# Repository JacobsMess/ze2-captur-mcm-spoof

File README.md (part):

# ZE2 Captur MCM spoof board

> **Current version: v0.11, the head of `main`.** Everything in this
> repository (board, fab files in `hw/out/jlc/`, firmware, images, docs) describes v0.11. Earlier versions are kept
> only in the git history and are **superseded: do not order from them**. See [Versions](#versions).

A man-in-the-middle board that lets a stock Honda Insight ZE2 run on a Renault Captur E-Tech
lithium pack. The stock MCM stays in charge; the board only changes what it measures: cell taps,
pack temperatures and the current-sensor signal. It also sits on the car's CAN buses. Later,
with the MCM removed, the same board becomes the CAN gateway for a ZombieVerter and a Toyota
inverter.

> **Status: untested design, v0.11.** No boards have been made. v0.6, v0.7 and v0.10 fold in three design reviews;
> v0.8 lets the board measure or cope with the remaining unknowns itself; v0.9 moved the routing to
> [KiCadRoutingTools](https://github.com/drandyhaas/KiCadRoutingTools); v0.11 applies the VND7050AJ, Littelfuse 242,
> TPS3431 and ESP32-S3 datasheets (precharge-coil current sense, 100 ohm tap-ladder ends, fuse land pattern). Bring-up and vehicle checks are in
> [docs/BRINGUP.md](docs/BRINGUP.md). Several parts are placeholders (listed
> [below](#before-ordering)). The BOM carries LCSC numbers, Basic or Preferred wherever JLC has one. The design was
> produced with an AI assistant from my brief and is up for review ([feedback](#feedback) welcome).
> Don't connect it to a pack on the strength of this README.

| | |
|---|---|
| Car | Honda Insight ZE2 (JDM), stock IMA: MCM, MPI, DC-DC, junction board |
| Pack | Renault Captur E-Tech 1.2 kWh, 68S (2 x 34S), own master/satellite BMS and contactors |
| Stage 1 | modules in parallel, 34S2P, about 130 V; stock MCM fed spoofed signals |
| Stage 2 | 68S, about 260 V, MCM removed, ZombieVerter V1 + Toyota inverter (OpenInverter logic board) |
| MCU | ESP32-S3-WROOM-1-N8R2 (8 MB flash, Wi-Fi: SavvyCAN streaming over GVRET, OTA updates) |
| CAN | 4 buses: CAN1 EV (TWAI), CAN2/CAN3 the MCM and PCM halves of the IMA bus, CAN4 dash tap (MCP2518FD each, 32-frame receive FIFO) |
| Spoofing | 9 cell taps (resistor divider off the real pack bus), 3 NTC lines (DAC + op-amps), Hall current offset (+/-125 mV) |
| Contactors | Captur contactors and precharge driven by the board: high-side drivers + low-side master FET behind a watchdog-cleared enable latch |
| HV side | stage 1 only, rated 150 V, 5.6 mm copper-free band, short slots under the three isolation parts |
| Board | 120 x 98 mm, 4 layers, 1.6 mm, parts on top |

## How it works

- **Cell taps:** a resistor divider fed from the real pack bus (through a 250 V DC fuse and 100 ohm at
  each end, switched by two optoMOS) gives the MCM nine balanced taps. The taps are switched on only once
  the contactors are verified closed and the analog island is answering. If the board loses power the
  optoMOS open, the taps float and the MCM sets the IMA light and stops using the pack.
- **Temperatures:** a DAC and op-amp buffers drive the three NTC lines, mapping the Captur
  temperatures onto the Honda curve.
- **SOC:** a small DAC offset added to the Hall sensor signal nudges the MCM's own coulomb count to
  track the real pack, so it stops regen near full and assist near empty by itself.
- **Analog island:** the DAC, op-amps and readback ADCs run from the MCM's 5 V sensor supply,
  isolated from the rest by an I2C isolator, so everything is ratiometric to the MCM.
- **Captur contactors:** closed by the board at key-on, before the MCM looks at the pack. An
  AMC3311 isolated amplifier (with its own isolated supply) on the bus checks precharge and
  contactor welding.
- **CAN:** CAN2 and CAN3 split the IMA bus. A DPDT relay (K4) joins the halves whenever the board is
  unpowered. Each split half can be terminated at the board end by a 120 ohm resistor, connected
  only while K4 is energised: the PCM side through K4's spare normally-open contacts, the MCM side
  through a photoMOS driven alongside the coil. Each has a solder jumper, open by default; measure
  CANH-CANL on each half with the bus split (about 120 ohm: close it; about 60 ohm: leave it).
  CAN4 is a plain tap on the dash bus. CAN2-4 transceivers stay in hardware silent mode until a
  solder jumper is closed. Bypass is the factory setting (`mitm` off in NVS); when splitting is enabled,
  K4 is energised only after both CAN controllers confirm normal mode, and a hung control loop is reset by
  the task watchdog, which releases K4.
- **Protection:** steer SOC first; then float the tap divider so the MCM faults; last, open the
  Captur contactors. The master enable is a flip-flop that the firmware's watchdog kicks clock
  in; if the firmware hangs the watchdog clears it. A stall is a latched fault: nothing closes again
  until a key-off, which the ADC reads with hysteresis and a 2 s dwell so a crank dip doesn't count.
  Contactor, sensing and weld faults all end the same way, as does losing the ignition reading for
  0.5 s. A reset while running (brownout, watchdog, panic) starts tripped and stays so until the next
  power cycle. No regen below about 5 C.
- **Closing the contactors:** the Captur has two, main+ and precharge; pack negative is hard-wired. With
  both coils off the link (watched by the AMC3311) must be dead, which rules out a weld. Then precharge,
  then main+ with precharge still held until it has picked up, then precharge off for 300 ms: the link
  must hold at the pack voltage. A charged link reads ~100 % with main+ open too, so the check is that it
  doesn't decay (calibrated on the bench, [BRINGUP](docs/BRINGUP.md)). The precharge driver's current sense
  must show coil current while precharging and none once closed. The close aborts, latched, on a
  precharge deadline, a link reading above the pack, or a soft trip before it finishes. A soft trip keeps a
  closed pack closed but never starts a close.
- **Captur BMS:** kept awake by the 0x0F5 frame every 20 ms (counter + CRC-8) and read with UDS (29-bit,
  read-only) for the extreme cells, the cell sum, temperatures and SOC, as decoded on the bench. The
  precharge target is the cell sum scaled to the series string (half of it in 34S2P), and the sum must
  agree with 68 x the extreme cells.
- **If the board dies:** the IMA bus rejoins and the dash is unaffected, but the pack drops out on
  purpose. The car runs engine-only with the IMA light, and the 12 V battery isn't charged (the
  DC-DC runs off the pack).

## Schematic

Block-level sheets with the key part values, drawn by [`docs/schematic.py`](docs/schematic.py).
The netlist itself is [`hw/parts.json`](hw/parts.json), written by
[`hw/build_board.py`](hw/build_board.py).

<details>
<summary><b>The five sheets</b></summary>

</details>

## Circuit board

The HV strip is on the right. Only three parts cross the gap to it, and each is an isolation part:
the two AQV214EH optoMOS (K2, K3) and the AMC3311 (U12). There is a
1.2 mm slot under each of those, where dirt or flux trapped under the body could bridge pads. At
150 V or less the 5.6 mm band gives enough creepage without a slot elsewhere. The pack terminal
J3 overhangs the top edge with its wire entry facing out, and the USB-C face sits about 0.85 mm past the bottom edge.

## Before ordering

- Pinouts to check against datasheets: VND7050AJ (custom PowerSSO-16 footprint in `hw/lib`),
  TPS3431, SN74LVC1G74 and SN74LVC1G17 (watchdog latch), SN74LV1T34 (5 V gate buffers), AMC3311, AQY212GS,
  H24VNT2B, and the SMMS0630 inductor on the SRP7028A land pattern.
- Land patterns drawn from datasheet dimensions (`hw/lib/ze2.pretty`): the AQV214EHA (Panasonic's 1.5 x 1.9 mm
  lands on 8.3 mm rows) and the Littelfuse 242 fuse (end-cap lands sized from the 3.0 x 8.4 mm body: check
  against Littelfuse's drawing).
- The Captur coils are measured: main 22.8 ohm (0.535 A at 12 V, pulls in at 5.5 V), precharge about
  56 ohm (0.2 A, 6.8 V), so the coil path carries under 0.8 A. Pump: any 12 V pump under about 3 A
  (see [Pump](#pump)); nothing to measure before ordering.
- Wire the pack as below (the coils have no internal diode, so driving them from the high side with the
  common pin 7 on the return is fine).
- K4: beep-test a G6K-2F-Y before fitting. Pins 3/6 must be the commons (IMA side), 2/7 the
  normally-closed contacts (MCM side).
- AMC3311 stock at JLC is low: check before ordering, or fit by hand.
- Check rotations in JLC's placement preview, especially U8/U9 (custom footprint).
- Conformal-coat the HV strip. Every HV-class net (bus, ladder, taps, sense chain) keeps 0.7 mm from the
  bus-negative side by a DRC rule (`hw/ze2-mcm-spoof.kicad_dru`); IPC-2221 B2 asks 0.6 mm uncoated at 101-150 V.
  Creepage across the assembled parts, the harness and the enclosure still needs checking on the built unit.
- J5 (USB-C): KiCad's footprint puts the peg holes 0.19 mm from pads A/B. Common on JLC boards, but check
  their NPTH-to-copper rule when ordering.
- Check the Captur BMS protects both parallel strings in 34S2P.
- Nothing on the car or the pack needs measuring before ordering. What used to be on this list is now
  handled by the board itself:
  - NTC pull-ups: measured by the board at each start-up and trimmed by readback (only the Honda sensor's
    curve is assumed; check it against the MCM's reported battery temperature in the first log).
  - Tap input impedance: the tap ladder is 10k (0.13 W), so even a 1 Mohm MCM input shifts a block by
    under 4 %. To check it anyway: ohms from each VHB pin to VHB0 at the MCM connector, MCM unplugged.
  - Hall sensor zero and scale: not needed. SOC steering is closed-loop on the MCM's own SOC.
  - IMA bus log: the board logs it in bypass mode (SavvyCAN over Wi-Fi), with nothing transmitted.
  - Bus-sense divider: 1 % parts and a 92 % close check, so no meter trim is needed (`HV_DIV_X1000` is
    there if you want one).
  - The link's bleed time constant, which the open-main check relies on: measured on the bench before the car
    ([BRINGUP](docs/BRINGUP.md)).

### Pump

Choose the pump later; the board handles the common kinds without changes, set in NVS (`pump_mode`):

| Pump | Wiring on J2 | `pump_mode` |
|---|---|---|
| 2-wire, brushless (most cheap 12 V pumps, OEM inverter pumps) | + to 13, - to 14 | 0, on/off (default) |
| 2-wire, brushed | + to 13, - to 14 | 1, PWM at 20 kHz |
| 3-wire PWM (Bosch-style signal input) | + to 13, ground to a spare GND, signal to 14 | 2, signal at 100 Hz (`pump_hz`, `pump_inv`) |

Keep it under about 3 A: F2 (5 A) also feeds the coils. The board reads the pump line back through a threshold
FET (R102/R103 into Q26's gate, Q26 pulling GPIO35 low), so the GPIO never sees the 12-16 V line, and it reports
an open circuit, a failed Q3, or a 3-wire pump that isn't pulling its signal up.

### Captur LV connector to J2

| Captur pin | Function | J2 pin (net) |
|---|---|---|
| 1 | BMS +12 V | 5 (BMS12V) |
| 6, 12 | Ground | 3, 4, 8 (GND) |
| 5 / 10 | CAN H / CAN L | 6 / 7 (CAN1H / CAN1L) |
| 8 | HVIL loop: link to pin 12, as on the bench | - |
| 7 | Common of both coils | 12 (COIL_RTN) |
| 3 | Precharge coil | 9 (COIL_PRE) |
| 4 | Main coil | 10 (COIL_MAINP) |
| - | (spare high side; no main- contactor) | 11 (COIL_MAINN), leave open |

## Ordering at JLCPCB

[`hw/out/jlc/`](hw/out/jlc/) has the gerbers, BOM and CPL. The BOM picks are in
[`hw/jlc_parts.py`](hw/jlc_parts.py) and [`cost.md`](hw/out/jlc/cost.md) has the estimate: about $53 of
parts per board (cost.md has the current figures; Standard charges $1.53 for every Basic and Extended type,
Economic $3.07 per Extended type). Order Standard PCBA with everything fitted: the ESP32-S3 module needs it, and
the CPL includes the five Molex/Phoenix connectors at their body centres for JLC's THT assembly (check pin 1 and
the mating side in JLC's preview). The AQV214EH optoMOS isn't stocked at JLC: global-source it. The TPS3431-Q1
(TPS3431SQDRBRQ1, C2878091) has low LCSC stock: get it allocated before ordering. Ask JLC for separate 2- and
5-board fully assembled quotes to see the fixed costs. The only passives kept
Extended on purpose are the 0.1 % tap-ladder resistors, which set how evenly the MCM sees the blocks.

## Firmware

ESP-IDF firmware in [`firmware/`](firmware/), which builds cleanly but hasn't run on a board yet. It
covers all four CAN buses, the IMA man-in-the-middle, the spoofing, contactor sequencing and the
protection ladder. It also streams everything to SavvyCAN over Wi-Fi (GVRET) and takes firmware updates
over Wi-Fi with rollback, accepted only with the ignition off and the contactors open. SavvyCAN can only
transmit in that state too.

A simulation build runs the real firmware against modelled buses and MCP2518FDs on Espressif's ESP32-S3
QEMU, with all four buses up to 100 % load. No frames are lost at realistic loads, where core 1 (CAN)
runs at 22-70 % and core 0 at 18-37 %; with every bus saturated on the slow CPU model it is at the edge. See [`firmware/README.md`](firmware/README.md) for the
numbers.

## Building from source

Everything is generated by scripts in `hw/`; edit the scripts, not the KiCad files. With KiCad 7's Python
(`pcbnew` importable) and a [KiCadRoutingTools](https://github.com/drandyhaas/KiCadRoutingTools) checkout with
its router built, one command rebuilds the board, the JLC files, the images and runs the tests:

```
KRT_DIR=<KiCadRoutingTools checkout> hw/build.sh        # ECO: keeps unchanged copper, re-routes the rest (minutes)
KRT_DIR=<KiCadRoutingTools checkout> hw/build.sh full   # routes everything from scratch (~30 min)
```

Add `RENDER=1` for the ray-traced renders (`pip install bpy`; `KICAD_3D_DIRS=<kicad 9 3dmodels>:<kicad 7 3dmodels>`).
The steps it runs, from `hw/`:

| Step | Command |
|---|---|
| net classes, custom rules | `python3 project.py ze2-mcm-spoof` |
| netlist + placement | `python3 build_board.py build/unrouted.kicad_pcb` (also writes `parts.json`) |
| route | `python3 krt_route.py build/unrouted.kicad_pcb build/routed.kicad_pcb [ze2-mcm-spoof.kicad_pcb]`: the USB and CAN pairs coupled, the crystal nets first on F.Cu, then the rest at real track widths; JLC standard rules, no via in or touching an SMD pad, keep-out on the HV band; anything left incomplete gets a finishing pass that may use In1 (GND plane) at a high cost. With the last argument only nets whose pads changed, whose copper touches a changed part, or that were incomplete are re-routed |
| dangling copper | `python3 cleanup.py build/routed.kicad_pcb` until it prints nothing |
| coil/pump copper | `python3 widen_power.py build/routed.kicad_pcb build/finished.kicad_pcb` (1.0 mm where DRC allows, else 0.75 mm) |
| silkscreen | `python3 tidy_silk.py build/finished.kicad_pcb build/tidy.kicad_pcb` |
| planes, DRC, JLC files | `python3 fab.py build/tidy.kicad_pcb ze2-mcm-spoof.kicad_pcb out/jlc` (LCSC picks from `jlc_parts.py`) |
| layer images | `python3 photo_render.py ze2-mcm-spoof.kicad_pcb ../docs/img/layers` |
| 3D render | `EXPORT_DIR=scene xvfb-run -a python3 render3d.py ze2-mcm-spoof.kicad_pcb ../docs/img/layers_top.png x`, then `python3 blender_render.py scene/scene.json ../docs/img/board 64 1800` |
| schematic sheets | `python3 ../docs/schematic.py` |
| tests | `python3 -m pytest` (from the repo root) |

The tests check: KiCad DRC is clean apart from two accepted items (footprint-library notices, and
the USB-C peg holes in KiCad's own footprint); no copper in the HV band except the three isolation
parts; slots only under those parts; J3 and USB-C overhangs; the antenna keep-out; silkscreen text size; the
CAN termination, bypass relay contacts, watchdog latch, 5 V gate drive, driver input pins and reverse
protection in the netlist; the full-bus 0.7 mm rule; the JLC files against the board, with an LCSC number on
every line and Basic/Preferred passives; and the firmware against the hardware (GPIO map, CAN clock and
bit timing, crystal load caps, HV divider scale, ADC1 inputs). `tests/host/` compiles the firmware's
safety chain (BMS decode, safety ladder, contactor sequencer, ignition) with gcc against a model of the
contactors, the watchdog latch and the bus sense, and runs 23 scenarios: a normal close, welds, main+ stuck open
(with the link partly and fully charged), a soft trip or an implausibly high link mid-close, a late precharge,
sensor loss (bus and ignition), a loop stall and resume, crank dips, a reset while running, island loss, a
millisecond-counter wrap, stale or inconsistent BMS data. 9 more cover the pump drive, the NTC lines and the
island-health report.

| Folder | Contents |
|---|---|
| `hw/` | generators, build script, KiCad board and project, `parts.json` netlist |
| `hw/out/` | JLC gerbers, BOM, CPL and the DRC report |
| `firmware/` | ESP-IDF firmware, simulation build and its results (`firmware/sim/out/`) |
| `docs/` | schematic script and the README images |
| `tests/` | pytest checks |

## Versions

Only the head of `main` is current. Earlier versions are kept in the git history for reference and are superseded: their
fab files, firmware and docs are out of date. None has been built yet.

| Version | Status | What changed |
|---|---|---|
| **v0.11** (`main`) | **Current** (unbuilt) | Datasheet pass: precharge-coil current sense, 100 R tap-ladder ends, Littelfuse 242 land pattern |
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
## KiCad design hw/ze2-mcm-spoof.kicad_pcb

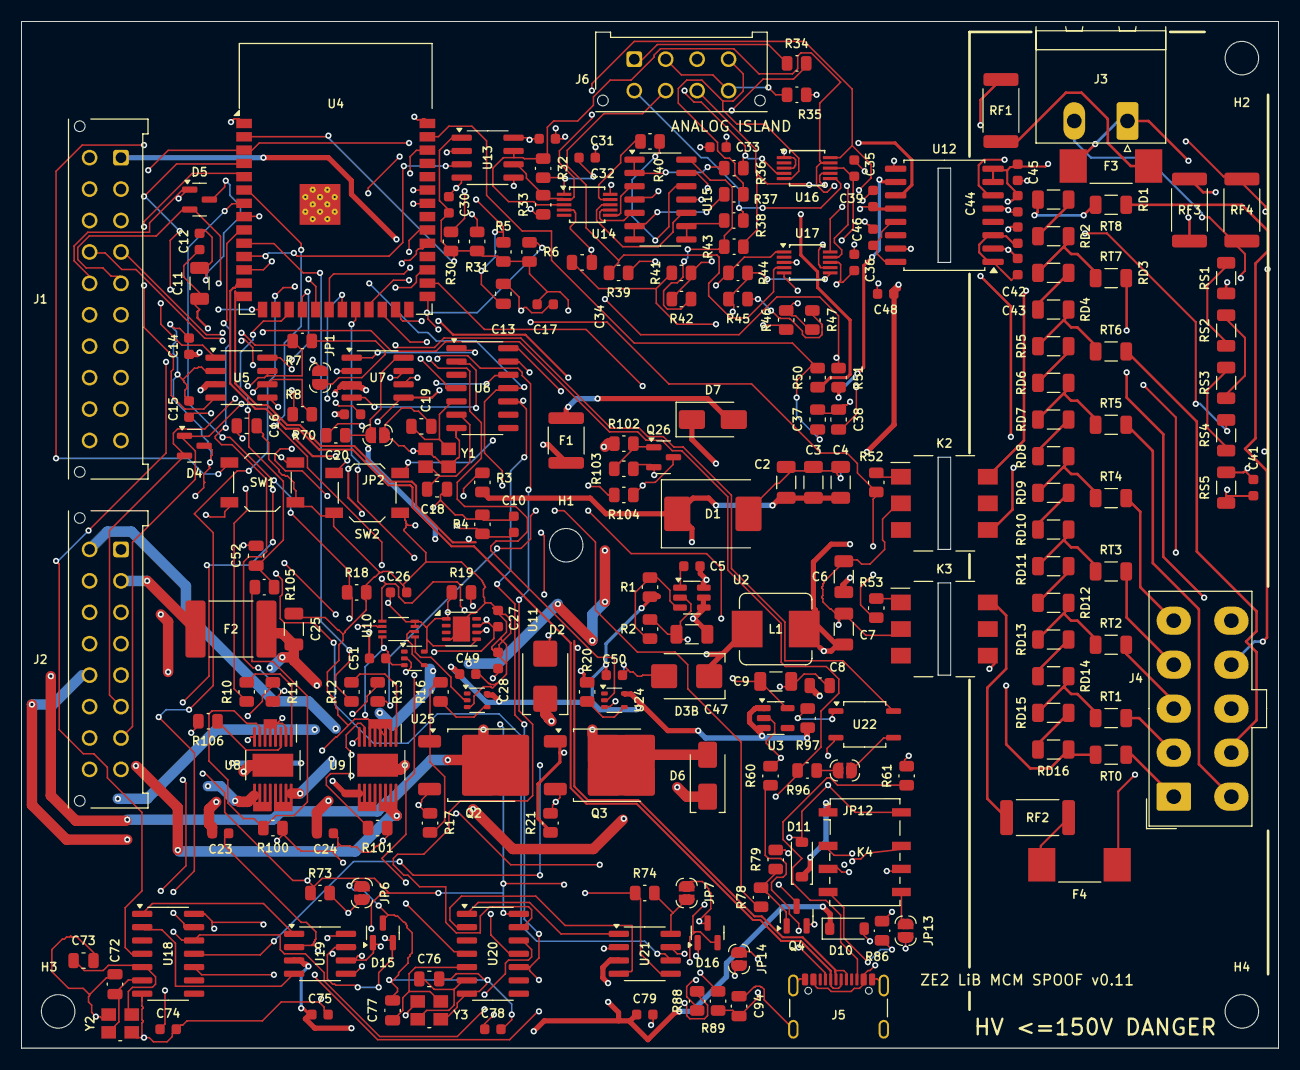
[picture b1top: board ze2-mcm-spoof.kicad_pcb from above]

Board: 4 copper layers, 120.0 x 98.0 mm, 218 parts (0 on the bottom side), 169 nets.

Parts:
C2, C3, C4, C25, C47: 10u 50V; C_1206_3216Metric
C5, C10, C12, C14, C15, C17, C20, C23, C24, C26, C27, C28, C30, C31, C32, C33, C35, C36, C44, C46, C49, C50, C51, C74, C75, C78, C79: 100n; C_0603_1608Metric
C6, C7: 22u; C_1206_3216Metric
C8, C13, C34: 1u; C_0805_2012Metric
C9, C11: 10u; C_1206_3216Metric
C16, C94: 4.7n; C_0805_2012Metric
C18, C19, C72, C73, C76, C77: 22p; C_0805_2012Metric
C37, C38, C52: 10n; C_0805_2012Metric
C39, C41, C43, C45: 1n; C_0603_1608Metric
C42, C48: 1u; C_0603_1608Metric
D1: SMCJ33CA; D_SMC
D2: SMBJ33A; D_SMB
D3B: SS36; D_SMB
D4, D5, D15, D16: H24VNT2B; SOT-23
D6, D7: SS54; D_SMA
D10: B5819W; D_SOD-123
D11: 1N4148W; D_SOD-123
F1: 2A PTC; Fuse_1812_4532Metric
F2: 5A; Fuse_2920_7451Metric
F3, F4: 50mA 250V; Fuse_Littelfuse_242_SMD_L8.4mm_D3.0mm
H1, H2, H3, H4: M3; MountingHole_3.2mm_M3
J1: J1 VEHICLE/MCM; Molex_Micro-Fit_3.0_43045-2012_2x10_P3.00mm_Vertical
J2: J2 CAPTUR LV; Molex_Micro-Fit_3.0_43045-1612_2x08_P3.00mm_Vertical
J3: J3 BUS; PhoenixContact_MSTBA_2,5_2-G-5,08_1x02_P5.08mm_Horizontal
J4: J4 TAPS; Molex_Mini-Fit_Jr_5566-10A_2x05_P4.20mm_Vertical
J5: USB-C; USB_C_Receptacle_GCT_USB4105-xx-A_16P_TopMnt_Horizontal
J6: J6 MCM ANALOG; Molex_Micro-Fit_3.0_43045-0812_2x04_P3.00mm_Vertical
JP1: TERM; SolderJumper-2_P1.3mm_Open_RoundedPad1.0x1.5mm
JP2: CAN2 TX EN; SolderJumper-2_P1.3mm_Open_RoundedPad1.0x1.5mm
JP6: CAN3 TX EN; SolderJumper-2_P1.3mm_Open_RoundedPad1.0x1.5mm
JP7: CAN4 TX EN; SolderJumper-2_P1.3mm_Open_RoundedPad1.0x1.5mm
JP12: TERM2; SolderJumper-2_P1.3mm_Open_RoundedPad1.0x1.5mm
JP13: TERM3; SolderJumper-2_P1.3mm_Open_RoundedPad1.0x1.5mm
JP14: TERM4; SolderJumper-2_P1.3mm_Open_RoundedPad1.0x1.5mm
K2, K3: AQV214EH; Panasonic_PhotoMOS_DIP6_SMD_W8.3mm
K4: G6K-2F-Y 5VDC; Relay_DPDT_Omron_G6K-2F-Y
L1: 22uH; L_Bourns_SRP7028A_7.3x6.6mm
Q2, Q3: NCE6020AK; TO-252-2
Q4, Q26: 2N7002; SOT-23
R1: 56k; R_0805_2012Metric
R2, R5, R6, R39, R42, R44, R45, R46, R47, R70, R73, R74, R104: 10k; R_0805_2012Metric
R3, R17, R18, R19, R21, R79, R103: 100k; R_0805_2012Metric
R4: 22k; R_0805_2012Metric
R7, R8, R88, R89: 56; R_0805_2012Metric
R10, R11, R12, R13, R30, R31, R32, R33: 4.7k; R_0805_2012Metric
R16, R20, R43, R50, R51, R78: 100; R_0805_2012Metric
R34, R35: 0; R_0805_2012Metric
R36, R37, R38, R100, R101: 1k; R_0805_2012Metric
R40, R41, R102: 200k; R_0805_2012Metric
R52, R53: 270; R_0805_2012Metric
R60, R61: 5.1k; R_0805_2012Metric
R86, R96: 120; R_0805_2012Metric
R97: 470; R_0805_2012Metric
R105, R106: 15k; R_0805_2012Metric
RD1, RD2, RD3, RD4, RD5, RD6, RD7, RD8, RD9, RD10, RD11, RD12, RD13, RD14, RD15, RD16: 10k; R_1206_3216Metric
RF1, RF2: 100 1W; R_2512_6332Metric
RF3, RF4: 10k 1W; R_2512_6332Metric
RS1, RS2, RS3, RS4: 100k; R_1206_3216Metric
RS5: 4.7k; R_1206_3216Metric
RT0, RT1, RT2, RT3, RT4, RT5, RT6, RT7, RT8: 0; R_1206_3216Metric
SW1: RESET; SW_SPST_TL3342
SW2: BOOT; SW_SPST_TL3342
U2: LMR16006Y-Q1; SOT-23-6
U3: TLV75733PDBV; SOT-23-5
U4: ESP32-S3-WROOM-1-N8R2; ESP32-S3-WROOM-1
U5, U7, U19, U21: TJA1051T/3; SOIC-8_3.9x4.9mm_P1.27mm
U6, U18, U20: MCP2518FD; SOIC-14_3.9x8.7mm_P1.27mm
U8: VND7050AJ; ST_PowerSSO-16_3.9x4.9mm_P0.5mm_EP2.2x3.9mm_GND4-6
U9: VND7050AJ; ST_PowerSSO-16_3.9x4.9mm_P0.5mm_EP2.2x3.9mm
U10: 74LVC1G74; VSSOP-8_2.3x2mm_P0.5mm
U11: TPS3431-Q1; VSON-8-1EP_3x3mm_P0.65mm_EP1.65x2.4mm
U12: AMC3311; SOIC-16W_7.5x10.3mm_P1.27mm
U13: ISO1540; SOIC-8_3.9x4.9mm_P1.27mm
U14: MCP4728; MSOP-10_3x3mm_P0.5mm
U15: MCP6004; SOIC-14_3.9x8.7mm_P1.27mm
U16, U17: ADS1115; MSOP-10_3x3mm_P0.5mm
U22: AQY212GS; SOP-4_3.8x4.1mm_P2.54mm
U23, U24: SN74LV1T34; SOT-353_SC-70-5
U25: 74LVC1G17; SOT-353_SC-70-5
Y1, Y2, Y3: 40MHz; Crystal_SMD_3225-4Pin_3.2x2.5mm

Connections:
+3V3: C9.1, C11.1, C12.1, C15.1, C17.1, C26.1, C28.1, C30.1, C51.1, C74.1, C78.1, R5.1, R6.1, R19.1, R30.1, R31.1, R70.1, R73.1, R74.1, R104.1, R106.1, U3.5, U4.2, U5.5, U6.14, U7.5, U10.7, U10.8, U11.1, U11.5, U13.1, U18.14, U19.5, U20.14, U21.5, U25.5
+5V: C6.1, C7.1, C8.1, C14.1, C20.1, C39.1, C48.2, C49.1, C50.1, C75.1, C79.1, D10.1, D11.1, K4.1, L1.2, R1.1, R97.1, U3.1, U3.3, U5.3, U7.3, U12.12, U19.3, U21.3, U23.5, U24.5
AMC_LDO: C46.1, U12.13, U12.16
AMC_N: C38.1, R51.2, U4.38
AMC_OUTN: R51.1, U12.10
AMC_OUTP: R50.1, U12.11
AMC_P: C37.1, R50.2, U4.39
BMS12V: J2.5, U9.9, U9.10, U9.11, U9.12
BOOT: R6.2, SW2.1, U4.27
BUCK_CB: C5.1, U2.1
BUCK_FB: R1.2, R2.1, U2.3
BUCK_SW: C5.2, D3B.1, L1.1, U2.6
BUS_N: F4.2, J3.2, RF4.1
BUS_N_F: C41.2, C42.2, C43.2, C44.2, C45.2, RF4.2, RS5.2, U12.2, U12.7, U12.8
BUS_N_FS: F4.1, RF2.2
BUS_P: F3.1, J3.1, RF3.1
BUS_P_F: RF3.2, RS1.1
BUS_P_FS: F3.2, RF1.1
CAN1H: D4.2, J1.4, J2.6, R7.1, U5.7
CAN1L: D4.1, J1.14, J2.7, R8.2, U5.6
CAN1_TERM: JP1.1, R7.2
CAN1_TERM_MID: C16.1, JP1.2, R8.1
CAN2_INT: U4.31, U6.4
CAN2_RXD: U6.2, U7.4
CAN2_S: JP2.1, R70.2, U7.8
CAN2_TXD: U6.1, U7.1
CAN3_INT: U4.15, U18.4
CAN3_RXD: U18.2, U19.4
CAN3_S: JP6.1, R73.2, U19.8
CAN3_TXD: U18.1, U19.1
CAN4_INT: U4.22, U20.4
CAN4_RXD: U20.2, U21.4
CAN4_S: JP7.1, R74.2, U21.8
CAN4_TXD: U20.1, U21.1
CC1: J5.A5, R60.1
CC2: J5.B5, R61.1
COIL_MAINN: J2.11, U9.13, U9.14, U9.15, U9.16
COIL_MAINP: J2.10, U8.9, U8.10, U8.11, U8.12
COIL_PRE: J2.9, U8.13, U8.14, U8.15, U8.16
COIL_RTN: D2.1, J2.12, Q2.2
DAC_A: U14.6, U15.3
DAC_B: U14.7, U15.5
DAC_C: U14.8, U15.10
DAC_D: R40.1, U14.9
DASH_CANH: D16.2, J1.6, R88.1, U21.7
DASH_CANL: D16.1, J1.16, R89.2, U21.6
DIVM0: RD1.2, RD2.1
DIVM1: RD3.2, RD4.1
DIVM2: RD5.2, RD6.1
DIVM3: RD7.2, RD8.1
DIVM4: RD9.2, RD10.1
DIVM5: RD11.2, RD12.1
DIVM6: RD13.2, RD14.1
DIVM7: RD15.2, RD16.1
DIV_BOT: K3.4, RD16.2, RT0.1
DIV_BOT_IN: K3.6, RF2.1
DIV_TOP: K2.6, RD1.1, RT8.1
DIV_TOP_IN: K2.4, RF1.2
ESP_EN: C13.1, R5.2, SW1.1, U4.3
GND: C2.2, C3.2, C4.2, C6.2, C7.2, C8.2, C9.2, C10.2, C11.2, C12.2, C13.2, C14.2, C15.2, C16.2, C17.2, C18.2, C19.2, C20.2, C23.2, C24.2, C25.2, C26.2, C27.2, C28.2, C30.2, C37.2, C38.2, C39.2, C46.2, C47.2, C48.1, C49.2, C50.2, C51.2, C52.2, C72.2, C73.2, C74.2, C75.2, C76.2, C77.2, C78.2, C79.2, C94.2, D1.2, D2.2, D3B.2, D4.3, D5.3, D15.3, D16.3, J1.2, J1.11, J1.12, J2.3, J2.4, J2.8, J5.A1, J5.A12, J5.B1, J5.B12, J5.S1, JP2.2, JP6.2, JP7.2, K2.2, K3.2, Q2.3, Q3.3, Q4.2, Q26.2, R2.2, R4.2, R17.2, R18.2, R21.2, R60.2, R61.2, R79.2, R100.2, R101.2, R103.2, SW1.2, SW2.2, U2.2, U3.2, U4.1, U4.40, U4.41, U5.2, U5.8, U6.7, U7.2, U8.2, U8.4, U8.5, U8.6, U9.2, U9.3, U9.4, U9.5, U9.6, U10.4, U11.4, U11.9, U12.9, U12.15, U13.4, U18.7, U19.2, U20.7, U21.2, U23.3, U24.3, U25.3, Y1.2, Y1.4, Y2.2, Y2.4, Y3.2, Y3.4
HS_BMS: R13.1, U4.23
HS_BMS_R: R13.2, U9.8
HS_MAINN: R12.1, U4.10
HS_MAINN_R: R12.2, U9.1
HS_MAINP: R11.1, U4.9
HS_MAINP_R: R11.2, U8.8
HS_PRE: R10.1, U4.8
HS_PRE_R: R10.2, U8.1
HV5V: C42.1, C43.1, U12.1, U12.3
HV5V_LDO: C44.1, C45.1, U12.5
IG_SENSE: C10.1, R3.2, R4.1, U4.18
IMA_CANH: D15.2, J1.3, K4.3, U19.7
IMA_CANL: D15.1, J1.13, K4.6, U19.6
ISL5V: C31.1, C32.1, C33.1, C35.1, C36.1, R32.1, R33.1, R34.2, R44.1, R46.1, U13.8, U14.1, U15.4, U16.8, U17.1, U17.8
ISL5V_HALF: R46.2, R47.1, U17.5
ISLGND: C31.2, C32.2, C33.2, C34.2, C35.2, C36.2, R35.2, R45.2, R47.2, U13.5, U14.4, U14.10, U15.11, U16.1, U16.3, U17.3, U17.7
ISOC_IN: J6.6, R39.1, U17.4
ISOC_OUT: J6.7, R43.2, U16.7
K2_LED: K2.1, R52.2
K3_LED: K3.1, R53.2
K4_COIL: D11.2, K4.8, Q4.3, U22.2
K4_NO1: K4.4, R86.1
K4_NO2: JP13.2, K4.5
MASTER_EN: U10.5, U23.2
MCM5V: J6.1, R34.1
MCM_CANH: D5.2, J1.5, K4.2, R96.1, U7.7
MCM_CANL: D5.1, J1.15, K4.7, U7.6, U22.4
MCM_SG: J6.2, J6.8, R35.1
MCU_EN: R18.1, U4.7, U10.2
MSENSE_U8: R100.1, R105.1, U8.7
MSENSE_U9: R101.1, U9.7
MS_ADC: C52.1, R105.2, U4.17
MS_SEN: R106.2, U8.3
OPTO_EN: R52.1, R53.1, U4.34
OSC1: C18.1, U6.6, Y1.1
OSC2: C19.1, U6.5, Y1.3
OSC3_1: C72.1, U18.6, Y2.1
OSC3_2: C73.1, U18.5, Y2.3
OSC4_1: C76.1, U20.6, Y3.1
OSC4_2: C77.1, U20.5, Y3.3
OUTA: R36.1, U15.1, U15.2
OUTB: R37.1, U15.6, U15.7
OUTC: R38.1, U15.8, U15.9
OUTD: R42.2, R43.1, U15.14
PUMP_G: Q26.1, R102.2, R103.1
PUMP_N: D6.2, J2.14, Q3.2, R102.1
PUMP_PWM: U4.24, U24.2
PUMP_SENSE: Q26.3, R104.2, U4.28
Q2_DRV: R16.1, U23.4
Q2_G: Q2.1, R16.2, R17.1
Q3_DRV: R20.1, U24.4
Q3_G: Q3.1, R20.2, R21.1
Q4_G: Q4.1, R78.2, R79.1
RELAY_SPLIT: R78.1, U4.35
SCL1: R31.2, U4.11, U13.3
SCL2: R33.2, U13.6, U14.2, U16.10, U17.10
SDA1: R30.2, U4.12, U13.2
SDA2: R32.2, U13.7, U14.3, U16.9, U17.9
SENSE_MID: C41.1, RS4.2, RS5.1, U12.6
SNS1: RS1.2, RS2.1
SNS2: RS2.2, RS3.1
SNS3: RS3.2, RS4.1
SPI_CS: U4.32, U6.13
SPI_CS3: U4.29, U18.13
SPI_CS4: U4.25, U20.13
SPI_MISO: U4.21, U6.12, U18.12, U20.12
SPI_MOSI: U4.19, U6.11, U18.11, U20.11
SPI_SCK: U4.20, U6.10, U18.10, U20.10
SUM_N: R41.2, R42.1, U15.13
SUM_P: R39.2, R40.2, U15.12
TAP1: RD14.2, RD15.1, RT1.1
TAP2: RD12.2, RD13.1, RT2.1
TAP3: RD10.2, RD11.1, RT3.1
TAP4: RD8.2, RD9.1, RT4.1
TAP5: RD6.2, RD7.1, RT5.1
TAP6: RD4.2, RD5.1, RT6.1
TAP7: RD2.2, RD3.1, RT7.1
TBATT1: J6.3, R36.2, U16.4
TBATT2: J6.4, R37.2, U16.5
TBATT3: J6.5, R38.2, U16.6
TERM2: JP12.1, R96.2
TERM2_LED: R97.2, U22.1
TERM2_SW: JP12.2, U22.3
TERM3: JP13.1, R86.2
TERM4: JP14.1, R88.2
TERM4_MID: C94.1, JP14.2, R89.1
TWAI_RX: U4.5, U5.4
TWAI_TX: U4.4, U5.1
USB_DN: J5.A7, J5.B7, U4.13
USB_DP: J5.A6, J5.B6, U4.14
VBAT_P: C2.1, C3.1, C4.1, C47.1, D1.1, D7.1, R3.1, U2.4, U2.5
VBUS: D10.2, J5.A4, J5.A9, J5.B4, J5.B9
VCOIL: C23.1, C24.1, C25.1, D6.1, F2.2, J2.13, U8.17, U9.17
VCOIL_RAW: F2.1, J2.1, J2.2
VHB0: J4.1, RT0.2
VHB1: J4.2, RT1.2
VHB2: J4.3, RT2.2
VHB3: J4.4, RT3.2
VHB4: J4.5, RT4.2
VHB5: J4.6, RT5.2
VHB6: J4.7, RT6.2
VHB7: J4.8, RT7.2
VHB8: J4.9, RT8.2
VIG_F: D7.2, F1.2
VIG_RAW: F1.1, J1.1
VMID: C34.1, R41.1, R44.2, R45.1, U17.6
WDI: U4.6, U10.1, U11.6
WDT_CLR: U10.6, U25.4
WDT_OK: C27.1, R19.2, U11.7, U25.2

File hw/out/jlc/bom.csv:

Comment,Designator,Footprint,LCSC Part #,Qty,Class,MPN,Unit USD,Notes
10u 50V,"C2,C3,C4,C25,C47",C_1206_3216Metric,C13585,5,B,CL31A106KBHNNNE 50V X5R,0.040,
100n,"C5,C10,C12,C14,C15,C17,C20,C23,C24,C26,C27,C28,C30,C31,C32,C33,C35,C36,C44,C46,C49,C50,C51,C74,C75,C78,C79",C_0603_1608Metric,C14663,27,B,CC0603KRX7R9BB104 50V X7R,0.002,
22u,"C6,C7",C_1206_3216Metric,C12891,2,B,CL31A226KAHNNNE 25V X5R,0.030,
1u,"C8,C13,C34",C_0805_2012Metric,C28323,3,B,CL21B105KBFNNNE 50V X7R,0.009,
10u,"C9,C11",C_1206_3216Metric,C13585,2,B,CL31A106KBHNNNE 50V X5R,0.040,
4.7n,"C16,C94",C_0805_2012Metric,C1744,2,B,0805B472K500NT 50V X7R,0.002,
22p,"C18,C19,C72,C73,C76,C77",C_0805_2012Metric,C1804,6,B,CL21C220JBANNNC 50V C0G,0.003,
10n,"C37,C38,C52",C_0805_2012Metric,C1710,3,B,CL21B103KBANNNC 50V X7R,0.002,
1n,"C39,C41,C43,C45",C_0603_1608Metric,C1588,4,B,CL10B102KB8NNNC 50V X7R,0.002,
1u,"C42,C48",C_0603_1608Metric,C15849,2,B,CL10A105KB8NNNC 50V X5R,0.004,
SMCJ33CA,D1,D_SMC,C19077608,1,P,SMCJ33CA,0.133,
SMBJ33A,D2,D_SMB,C19077586,1,P,SMBJ33A,0.051,
H24VNT2B,"D4,D5,D15,D16",SOT-23,C20615827,4,P,H24VNT2B,0.059,
SS54,"D6,D7",D_SMA,C22452,2,B,SS54,0.045,
B5819W,D10,D_SOD-123,C64885,1,P,B5819W,0.020,
1N4148W,D11,D_SOD-123,C81598,1,B,1N4148W,0.012,
SS36,D3B,D_SMB,C18199182,1,P,SS36B,0.049,
2A PTC,F1,Fuse_1812_4532Metric,C960026,1,E,BSMD1812-200-30V,0.110,
5A,F2,Fuse_2920_7451Metric,C19078763,1,E,2920L500/30GR,0.161,
50mA 250V,"F3,F4",Fuse_Littelfuse_242_SMD_L8.4mm_D3.0mm,C178911,2,E,Littelfuse 0242.050UR 250 VAC/VDC 4 kA,2.600,
J1 VEHICLE/MCM,J1,Molex_Micro-Fit_3.0_43045-2012_2x10_P3.00mm_Vertical,C485575,1,E,Molex 430452012,2.627,THT
J2 CAPTUR LV,J2,Molex_Micro-Fit_3.0_43045-1612_2x08_P3.00mm_Vertical,C491447,1,E,Molex 430451612,1.179,THT
J3 BUS,J3,"PhoenixContact_MSTBA_2,5_2-G-5,08_1x02_P5.08mm_Horizontal",C90074,1,E,Phoenix 1757242,0.273,THT
J4 TAPS,J4,Molex_Mini-Fit_Jr_5566-10A_2x05_P4.20mm_Vertical,C504844,1,E,Molex 39288100 (check peg holes),0.516,THT
USB-C,J5,USB_C_Receptacle_GCT_USB4105-xx-A_16P_TopMnt_Horizontal,C3020560,1,E,USB4105-GF-A,1.023,
J6 MCM ANALOG,J6,Molex_Micro-Fit_3.0_43045-0812_2x04_P3.00mm_Vertical,C277661,1,E,Molex 430450812,0.605,THT
AQV214EH,"K2,K3",Panasonic_PhotoMOS_DIP6_SMD_W8.3mm,,2,G,AQV214EHAX,3.000,not stocked at JLC: global sourcing or hand fit
G6K-2F-Y 5VDC,K4,Relay_DPDT_Omron_G6K-2F-Y,C47190,1,E,G6K-2F-Y-TR DC5,1.049,"COM 3/6 = PCM side, NC 2/7 = MCM side, NO 4/5 = PCM termination; beep it out before fitting"
22uH,L1,L_Bourns_SRP7028A_7.3x6.6mm,C128694,1,E,SMMS0630-220M 2.6A,0.085,
NCE6020AK,"Q2,Q3",TO-252-2,C108639,2,E,NCE6020AK,0.156,
2N7002,"Q4,Q26",SOT-23,C8545,2,B,2N7002,0.018,
56k,R1,R_0805_2012Metric,C17756,1,P,0805W8F5602T5E 1%,0.002,
10k,"R2,R5,R6,R39,R42,R44,R45,R46,R47,R70,R73,R74,R104",R_0805_2012Metric,C17414,13,B,0805W8F1002T5E 1%,0.002,
100k,"R3,R17,R18,R19,R21,R79,R103",R_0805_2012Metric,C149504,7,B,0805W8F1003T5E 1%,0.002,
22k,R4,R_0805_2012Metric,C17560,1,B,0805W8F2202T5E 1%,0.002,
56,"R7,R8,R88,R89",R_0805_2012Metric,C17757,4,P,0805W8F560JT5E 1%,0.002,
4.7k,"R10,R11,R12,R13,R30,R31,R32,R33",R_0805_2012Metric,C17673,8,B,0805W8F4701T5E 1%,0.002,
100,"R16,R20,R43,R50,R51,R78",R_0805_2012Metric,C17408,6,B,0805W8F1000T5E 1%,0.002,
0,"R34,R35",R_0805_2012Metric,C17477,2,B,0805W8F0000T5E,0.002,
1k,"R36,R37,R38,R100,R101",R_0805_2012Metric,C17513,5,B,0805W8F1001T5E 1%,0.002,
200k,"R40,R41,R102",R_0805_2012Metric,C17539,3,B,0805W8F2003T5E 1%,0.002,
270,"R52,R53",R_0805_2012Metric,C17590,2,P,0805W8F2700T5E 1%,0.002,
5.1k,"R60,R61",R_0805_2012Metric,C27834,2,B,0805W8F5101T5E 1%,0.002,
120,"R86,R96",R_0805_2012Metric,C17437,2,B,0805W8F1200T5E 1%,0.002,
470,R97,R_0805_2012Metric,C17710,1,B,0805W8F4700T5E 1%,0.002,
15k,"R105,R106",R_0805_2012Metric,C17475,2,B,0805W8F1502T5E 1%,0.002,
10k,"RD1,RD2,RD3,RD4,RD5,RD6,RD7,RD8,RD9,RD10,RD11,RD12,RD13,RD14,RD15,RD16",R_1206_3216Metric,C406729,16,E,ARG06BTC1002 0.1% 25ppm,0.050,
100 1W,"RF1,RF2",R_2512_6332Metric,C35218,2,E,25121WF1000T4E 1W 1%,0.020,
10k 1W,"RF3,RF4",R_2512_6332Metric,C270956,2,E,25121WF1002T4E 1W 1%,0.023,
100k,"RS1,RS2,RS3,RS4",R_1206_3216Metric,C17900,4,B,1206W4F1003T5E 1%,0.003,
4.7k,RS5,R_1206_3216Metric,C17936,1,B,1206W4F4701T5E 1%,0.003,
0,"RT0,RT1,RT2,RT3,RT4,RT5,RT6,RT7,RT8",R_1206_3216Metric,C17888,9,B,1206W4F0000T5E,0.003,
RESET,SW1,SW_SPST_TL3342,C318884,1,B,TS-1187A-B-A-B,0.021,
BOOT,SW2,SW_SPST_TL3342,C318884,1,B,TS-1187A-B-A-B,0.021,
LMR16006Y-Q1,U2,SOT-23-6,C544521,1,E,LMR16006YQDDCRQ1,0.885,
TLV75733PDBV,U3,SOT-23-5,C485517,1,E,TLV75733PDBVR,0.201,
ESP32-S3-WROOM-1-N8R2,U4,ESP32-S3-WROOM-1,C2913204,1,E,ESP32-S3-WROOM-1-N8R2,4.599,
TJA1051T/3,"U5,U7,U19,U21",SOIC-8_3.9x4.9mm_P1.27mm,C38695,4,E,TJA1051T/3/1J,0.580,"CAN2 = IMA bus, MCM side. S pulled high (silent) until JP2 closed; CAN3: S pulled high (silent) until JP6 closed; CAN4: S pulled high (silent) until JP7 closed"
MCP2518FD,"U6,U18,U20",SOIC-14_3.9x8.7mm_P1.27mm,C626758,3,E,MCP2518FDT-E/SL,1.508,
VND7050AJ,U8,ST_PowerSSO-16_3.9x4.9mm_P0.5mm_EP2.2x3.9mm_GND4-6,C443997,1,E,VND7050AJTR,1.659,
VND7050AJ,U9,ST_PowerSSO-16_3.9x4.9mm_P0.5mm_EP2.2x3.9mm,C443997,1,E,VND7050AJTR,1.659,
74LVC1G74,U10,VSSOP-8_2.3x2mm_P0.5mm,C70285,1,E,SN74LVC1G74DCUR,0.250,
TPS3431-Q1,U11,VSON-8-1EP_3x3mm_P0.65mm_EP1.65x2.4mm,C2878091,1,E,TPS3431SQDRBRQ1 (low LCSC stock: allocate),0.890,
AMC3311,U12,SOIC-16W_7.5x10.3mm_P1.27mm,C22441843,1,E,AMC3311DWER (low JLC stock: check),5.856,"integrated isolated DC/DC; DWE 7.5 mm body, 8 mm creepage"
ISO1540,U13,SOIC-8_3.9x4.9mm_P1.27mm,C179739,1,E,ISO1540DR,0.957,
MCP4728,U14,MSOP-10_3x3mm_P0.5mm,C478093,1,E,MCP4728T-E/UN,2.637,
MCP6004,U15,SOIC-14_3.9x8.7mm_P1.27mm,C7378,1,E,MCP6004T-I/SL,0.487,
ADS1115,"U16,U17",MSOP-10_3x3mm_P0.5mm,C37593,2,E,ADS1115IDGSR,1.229,
AQY212GS,U22,SOP-4_3.8x4.1mm_P2.54mm,C719745,1,E,AQY212GS,1.343,
SN74LV1T34,"U23,U24",SOT-353_SC-70-5,C78541,2,E,SN74LV1T34DCKR,0.080,
74LVC1G17,U25,SOT-353_SC-70-5,C10425,1,E,SN74LVC1G17DCKR,0.100,
40MHz,"Y1,Y2,Y3",Crystal_SMD_3225-4Pin_3.2x2.5mm,C9010,3,E,X322540MPB4SI 15pF,0.110,

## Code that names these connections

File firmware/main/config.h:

// Board pin map, timing and protocol constants. Pins follow hw/parts.json (ESP32-S3-WROOM-1 module pins
// mapped to GPIOs). The Honda IMA IDs are not known yet (they come from SavvyCAN logs of the stock car); until
// then the gateway passes IMA traffic through unchanged.
#pragma once
#include <stdint.h>
#include "sdkconfig.h"

#ifdef CONFIG_ZE2_SIM
#define ZE2_SIM 1
#else
#define ZE2_SIM 0
#endif

// ---------------------------------------------------------------- GPIO (module pin -> GPIO)
#define PIN_TWAI_TX      4   // pin 4  CAN1 (EV bus) TJA1051
#define PIN_TWAI_RX      5   // pin 5
#define PIN_WDI          6   // pin 6  TPS3431 watchdog kick; also U10 latch clock
#define PIN_MCU_EN       7   // pin 7  U10 latch D: contactor master enable, clocked in by WDI
#define PIN_HS_PRE       15  // pin 8  VND7050 precharge contactor
#define PIN_HS_MAINP     16  // pin 9  VND7050 main + contactor
#define PIN_HS_MAINN     17  // pin 10 VND7050 spare channel (the Captur has no main- contactor): never driven
#define PIN_I2C_SCL      18  // pin 11 to the analog island through ISO1540
#define PIN_I2C_SDA      8   // pin 12
#define PIN_CAN3_INT     3   // pin 15 MCP2518FD U18 (PCM side of the IMA bus)
#define PIN_MS_ADC       9   // pin 17 U8 MultiSense, precharge coil (1k R100, 15k R105, 10n C52), ADC1 ch8
#define PIN_IG_SENSE     10  // pin 18 board supply / 5.545 on ADC1 ch9 (ignition)
#define PIN_SPI_MOSI     11  // pin 19
#define PIN_SPI_SCK      12  // pin 20
#define PIN_SPI_MISO     13  // pin 21
#define PIN_CAN4_INT     14  // pin 22 MCP2518FD U20 (dash bus tap)
#define PIN_HS_BMS       21  // pin 23 Captur BMS 12 V feed
#define PIN_PUMP_PWM     47  // pin 24 coolant pump (U24 -> Q3)
#define PIN_PUMP_SENSE   35  // pin 28 Q26 drain (10k pull-up): LOW while the pump line is above ~6 V
#define PIN_SPI_CS4      48  // pin 25
#define PIN_SPI_CS3      36  // pin 29
#define PIN_CAN2_INT     38  // pin 31 MCP2518FD U6 (MCM side of the IMA bus)
#define PIN_SPI_CS2      39  // pin 32
#define PIN_OPTO_EN      41  // pin 34 tap-divider optoMOS K2/K3
#define PIN_RELAY_SPLIT  42  // pin 35 K4 bypass relay + U22 photoMOS (energised = IMA bus split)
#define PIN_AMC_P        1   // pin 39 AMC3311 output + (ADC1 ch0)
#define PIN_AMC_N        2   // pin 38 AMC3311 output - (ADC1 ch1)

// ---------------------------------------------------------------- buses
typedef enum { BUS_EV = 0, BUS_MCM = 1, BUS_PCM = 2, BUS_DASH = 3, BUS_COUNT = 4 } bus_id_t;
#define CAN_BITRATE        500000
#define MCP_SPI_HZ         16000000   // MCP2518FD: <= 0.85 x SYSCLK/2 = 17 MHz; 80 MHz / 5 on the S3
#define HV_DIV_X1000       90362      // (10k + 400k + 4.7k + 10k) / 4.7k incl. RF3/RF4; calibrate per board
#define MCP_OSC_HZ         40000000   // SYSCLK = crystal, PLL off

// ---------------------------------------------------------------- analog island (I2C)
#define I2C_HZ             400000
#define MCP4728_ADDR       0x60       // DAC: ch A-C NTC1-3 emulation, ch D current-sensor offset
#define ADS1115_A_ADDR     0x48       // readback: NTC lines, Hall in/out
#define ADS1115_B_ADDR     0x49       // readback: MCM 5 V, tap divider check
#define DAC_CH_OFFSET      3
#define AMC_CM_MIN_MV      1200       // AMC3311 output common mode 1.39-1.49 V, plus ADC error
#define AMC_CM_MAX_MV      1700
#define AMC_DIFF_MIN_MV    (-50)      // below: fail-safe output (HV side unpowered) or a fault
#define OFFSET_GAIN        0.05f      // summer: Vout = Vhall + 0.05 * (Vdac - Vmid)
#define OFFSET_MAX_MV      125.0f

// ---------------------------------------------------------------- pack and limits (34S2P stage 1)
#define PACK_SERIES        34
#define CELL_MAX_MV        4150       // soft limit (NMC); hard trip at +50 mV
#define CELL_MIN_MV        3100       // soft limit; hard trip at -100 mV
#define CELL_HARD_MAX_MV   4200
#define CELL_HARD_MIN_MV   3000
#define CHARGE_MIN_TEMP_C  5          // no regen (charge) below this
#define PACK_MAX_TEMP_C    55
#define PRECHARGE_PCT      90         // bus must reach this % of pack voltage
#define PRECHARGE_TIMEOUT_MS 3000
#define DEAD_BUS_MV        20000      // below this the link counts as dead (weld check)
#define MAIN_PICKUP_MS     100        // precharge held this long after main+ is commanded
#define CLOSE_VERIFY_MS    300        // then precharge off for this long: the link must hold up (below)
#define CLOSE_AVG_MS       50         // link averaged over the first and the last this-long of that window
#define CLOSED_MIN_PCT     92         // allows for the untrimmed 1 % bus-sense divider
// An open main+ with the link capacitance charged through precharge still reads ~100 %, so voltage alone can't
// prove closure. With precharge off it decays through the link's bleed: an open main+ shows as droop across
// the verify window, a closed one holds flat. Catches an open main+ if the link bleed time constant is under
// ~20 x CLOSE_VERIFY_MS / (CLOSE_DROOP_PM / 1000) = 4 s at these values; measure it (docs/BRINGUP.md) and
// tune before relying on it. 0 disables the check.
#define CLOSE_DROOP_PM     15         // per mille of pack voltage
// Precharge-coil current (U8 MultiSense channel 0: SEn tied high, SEL0/SEL1 low). Reading = Iout x
// COIL_SENSE_K_TYP / K, and K spreads 830-1935 at 0.2 A, so the window is wide: below the minimum the coil, its
// harness, the VND supply or the COIL_RTN master FET is open; above it the coil is shorted (an overloaded channel
// drives VSENSEH, 5-6.6 V, which clips the ADC at ~4 A equivalent). Limits cover 10-15 V and -40..+100 C coils.
// With precharge off and the master FET on the output sits at ~0 V and MultiSense is Hi-Z: any reading above
// COIL_OFF_MAX_MA means the high side is conducting while commanded off.
#define COIL_SENSE_K_TYP   1400       // IOUT / ISENSE, K0 typical (0.2 A)
#define COIL_SENSE_R       1000       // R100, ohm
#define COIL_SETTLE_MS     50         // coil on this long before its current counts (L/R and tDSENSE2H)
#define COIL_PRE_MIN_MA    60         // precharge coil: 0.21 A nominal (56 ohm, 12 V)
#define COIL_PRE_MAX_MA    700
#define COIL_OFF_MAX_MA    80         // ~57 mV at the ADC: clear of its zero error; check at bring-up
#define LINK_MAX_PCT       108        // link above pack x this % + LINK_MAX_EXTRA_MV: sensor or BMS data wrong
#define LINK_MAX_EXTRA_MV  4000
#define BUS_COLLAPSE_PCT   70         // closed, link below this % of pack: fault
#define PACK_TOL_PCT       3          // BMS cell sum vs 68 x cell range: 3 % + 2 V
#define PACK_TOL_MV        2000

// ---------------------------------------------------------------- ignition (board supply after D7)
#define VBAT_DIV_X1000     5545       // (100k + 22k) / 22k
#define IGN_ON_MV          9000       // key-on above this for IGN_ON_MS
#define IGN_ON_MS          100
#define IGN_OFF_MV         6000       // key-off below this for IGN_OFF_MS (rides through a crank dip)
#define IGN_OFF_MS         2000
#define IGN_INVALID_MS     500        // no valid ignition reading for this long: latched fault, contactors open

// ---------------------------------------------------------------- coolant pump (pump.h)
#define PUMP_PWM_HZ        20000      // 2-wire brushed pump chopped above audio
#define PUMP_SIGNAL_HZ     100        // 3-wire pump signal line
#define PUMP_MIN_DUTY      0.3f       // PWM mode: below this a brushed pump may stall
#define PUMP_SETTLE_MS     100        // Q3 steady this long before the line readback counts

// ---------------------------------------------------------------- timing
#define CONTROL_PERIOD_MS  10
#define WDI_PERIOD_MS      100        // TPS3431 kick: one rising edge per period (timeout 1.36 s min)
#define WDT_STALL_MS       600        // loop gap this long with coils energised: latched fault
#define BUS_SILENT_MS      500        // IMA half quiet this long -> drop back to bypass
#define GW_ARM_MS          100        // both CAN controllers must confirm normal mode within this, or no split
#define ISLAND_FAIL_MS     250        // no good DAC write + ADC readback for this long: taps float
#define BMS_TIMEOUT_MS     1000       // any Captur value older than this -> hard trip (normally < 150 ms)

// ---------------------------------------------------------------- CAN IDs
#define CAPTUR_KEEPALIVE_ID 0x0F5     // Captur BMS stays awake while this arrives (captur.h)
#define CAPTUR_KEEPALIVE_MS 20
#define CAPTUR_UDS_REQ     0x18DADBF1 // UDS read requests to the BMS (29-bit)
#define CAPTUR_UDS_RESP    0x18DAF1DB // its replies
#define ZV_ID_BMS_BASE     0x3E0      // stage 2: ZombieVerter "simpBMS"-style frames (check against ZV firmware)

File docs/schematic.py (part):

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        d += elm.Dot().label("+3V3", "top")

        mcu = ic(d, (10, -14), 6.5, 8.5, "U4 ESP32-S3-WROOM-1-N8R2\nWiFi: GVRET, web UI, OTA",
                 left=("SPI", "GPIO TWAI_RX", "GPIO TWAI_TX"),
                 right=("USB D+/D-", "IG_SENSE", "AMC3311 ADC", "OPTO_EN", "HS IN", "MCU_EN", "WDI", "I2C"))
        t1 = ic(d, (1.5, -8.6), 2.8, 2.2, "U5 TJA1051T/3\nCAN1 -> Captur BMS",
                left=("CANH", "CANL"), right=("TXD", "RXD"), bottom=("S",))
        wire(d, t1.TXD, mcu["GPIO TWAI_TX"], "-|")
        wire(d, t1.RXD, mcu["GPIO TWAI_RX"], "-|")
        d += elm.Line().at(t1.CANH).left(1.4).label("J2 CAN1_H", "left")
        d += elm.Line().at(t1.CANL).left(1.4).label("J2 CAN1_L", "left")
        d += elm.Line().at(t1.S).down(0.5)
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        wire(d, t2.TXD, mcp.TXCAN, "-")
        wire(d, t2.RXD, mcp.RXCAN, "-")
        wire(d, mcp.SPI, mcu.SPI, "-|")
        d += elm.Line().at(t2.CANH).left(1.4).label("J1 IMA_CANH", "left")
        d += elm.Line().at(t2.CANL).left(1.4).label("J1 IMA_CANL", "left")
        d += elm.Line().at(t2.S).down(0.6)
        d += elm.Dot().label("+3V3", "bottom")
        note(d, (-2.6, -18.6), "S tied HIGH = hardware SILENT mode: U7 cannot transmit.\nMCM-side termination is switched in only while split (sheet 5).")
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        note(d, (0, 3.2), "Sheet 2 - Captur contactor drivers, watchdog, pump", 15)
        d += elm.Dot(open=True).at((0, 0)).label("J2 COIL_12V\n(own fused feed)", "left")
        d += elm.Fuse().right().label("F2 5A")
        d += elm.Line().right(0.6).label("VCOIL", "top")
        chans = [("PRE", "U8A"), ("MAIN+", "U8B"), ("MAIN-", "U9A"), ("BMS_PWR", "U9B")]
        xs = [6, 10.5, 15, 19.5]
        d += elm.Line().at((3.0, 0)).to((xs[-1], 0))
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                d += (r := elm.Dot())
                rets.append(r.center)
        d += elm.Line().at(rets[0]).to(rets[-1])
        note(d, (rets[0][0], rets[0][1] - 0.3), "COIL_RTN = Captur pin 7 (coil common)", 8)
        d += elm.Line().at(rets[-1]).right(2.0)
        d += (rn := elm.Dot())
        d += elm.Zener().at(rn.center).right(2.2).reverse()
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        wire(d, buf.Y, q.gate, "-|")
        g = ic(d, (buf.A[0] - 4.4, buf.A[1] - 1.3), 2.4, 2.2, "U10 74LVC1G74 D-FF", left=("D", "CLK", "CLR"), right=("Q",), lab_loc="bottom")
        wire(d, g.Q, buf.A, "-|")
        d += elm.Line().at(g.D).left(1.4).label("MCU_EN", "left")
        d += elm.Line().at(g.CLK).left(1.4).label("WDI (MCU kick)", "left")
        st = ic(d, (g.CLR[0] - 3.0, g.CLR[1] + 0.5), 1.4, 1.0, "U25 LVC1G17", left=("A",), right=("Y",), lab_loc="bottom")
        wire(d, st.Y, g.CLR, "-|")
        wd = ic(d, (st.A[0] - 4.2, st.A[1] - 2.3), 2.4, 1.6, "U11 TPS3431\nwatchdog", left=("WDI",), right=("WDO",), lab_loc="bottom")
        wire(d, wd.WDO, st.A, "-|")
        d += elm.Line().at(wd.WDI).left(1.2).label("WDI", "left")

        note(d, (0, -14.5),
             "Every coil needs BOTH its high-side command AND the low-side master enable (MASTER_EN = latched MCU_EN).\n"
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             "U8 MultiSense ch0 = precharge-coil current: SEn via 15k (R106) to 3V3, SEL0/SEL1 low, 1k (R100) sense, 15k/10n (R105/C52) to IO9.\n"
             "U9 MultiSense unused (1k to GND, SEn low). Main+ closure is verified by the isolated bus sense (sheet 3). No flyback diodes.")

        d += elm.Dot(open=True).at((0, -18.5)).label("VCOIL", "left")
        d += elm.Line().right(2)
        d += (p1 := elm.Dot())
        d += elm.Line().right(2).label("J2 PUMP+", "right")
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        wire(d, ps.center, qs.G, "-")
        d += elm.Line().at(qs.D).right(1.0)
        d += (sd := elm.Dot())
        d += elm.Line().right(1.2).label("GPIO35 PUMP_SENSE (low = line above ~6 V)", "right", fontsize=8)
        d += elm.Resistor().at(sd.center).up(1.4)
        d += elm.Line().up(0.2).label("3V3 (R104 10k)", "right", fontsize=8)
        d += (qp := elm.NFet(bulk=False).at(p2.center).anchor("drain").down().reverse())
        d += elm.Ground().at(qp.source)
        d += elm.Line().at(qp.gate).left(1.0).label("PUMP_PWM via U24 (5 V)", "left")
        note(d, (p2.center[0] - 3.4, p2.center[1] - 1.0), "Q3 NCE6020AK", 8)
        note(d, (p2.center[0] + 5.6, p2.center[1] + 1.6), "2-wire pump: + PUMP+, - PUMP-\n3-wire PWM pump: + PUMP+, GND, signal on PUMP-\n(pump_mode in NVS)", 8)
        note(d, (11, -18.5),
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             "Bus 0-181V -> 0-2.0V (1% parts, ratio trimmed in firmware). Uses: weld check (dead link before a close),\n"
             "precharge (>=90% of BMS sum), closure (>=92% and no droop with precharge off), upper plausibility bound.\n"
             "Faults: a short below RF1/RF2 opens F3/F4 in ms (>=220 mA even tap-to-tap); RF3/RF4 hold any divider short within 1 W.\n\n"
             "8 segments fitted (9 taps). 7-segment car: link VHB8 to VHB7, J4 pin 9 unused.\n"
             "Opto LEDs from 3V3 via 330R, switched by OPTO_EN: MCU dead = divider floats\n"
             "= MCM sees no pack = safe IMA-off state.\n"
             "Divider load ~0.17 mA at 130V; zero drain with IG off.\nHV netclass 0.6 mm (IPC-2221 B2, uncoated, 101-150V); every HV net to the bus-negative side 0.7 mm.\n"
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
        # current summer
        y0 = -11.0
        d += elm.Dot(open=True).at((1.0, y0)).label("J6 ISOC_IN (Hall)", "left")
        d += elm.Resistor().right(3.0)
        note(d, (2.3, y0 + 0.8), "Ra 10k", 8)
        d += (nd := elm.Dot())
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        d += elm.Line().up(1.2)
        d += (f2 := elm.Dot())
        d += elm.Resistor().up(2.0)
        d += elm.Dot(open=True).label("Vmid 2.5V (10k/10k from MCM 5V)", "top", fontsize=8)
        note(d, (f2.center[0] + 0.4, f2.center[1] + 1.4), "Rg 200k", 8)
        rx = op.out[0] + 0.8
        d += elm.Line().at(f2.center).right(0.6)
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        d += elm.Line().to((rx, op.out[1]))
        d += elm.Dot()
        d += elm.Line().at(op.out).right(2.0)
        d += elm.Dot(open=True).label("J6 ISOC_OUT -> MCM", "right")

        note(d, (-3, -16.0),
             "Vout = Vhall + 0.05 x (Vdac - Vmid)  ->  +/-125 mV trim on the real sensor, full Hall bandwidth (pure analog path).\n"
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            d += elm.Dot().label(f"CAN{n}_S: 10k to 3V3 (silent), JP to GND = TX", "bottom", fontsize=8)
        note(d, (19.5, 0.8), "Per port: H24VNT2B ESD.\nCAN4 (dash tap): 2x56R + 4.7n split termination via JP14,\ndefault open; close only if the board replaces a bus-end node.\nCAN3: no fixed termination - switched by K4 below.")
        k4 = ic(d, (6, -16.5), 6.5, 3.6, "K4 Omron G6K-2F-Y 5V (DPDT)", left=("COM1", "COM2", "COIL+"), right=("NC1", "NC2", "NO1", "NO2", "COIL-"), lab_loc="bottom")
        d += elm.Line().at(k4.COM1).left(1.5).label("IMA_CANH (car / PCM side)", "left")
        d += elm.Line().at(k4.COM2).left(1.5).label("IMA_CANL", "left")
        d += elm.Line().at(k4.NC1).right(1.5).label("MCM_CANH (CAN2 / U7)", "right")
        d += elm.Line().at(k4.NC2).right(1.5).label("MCM_CANL", "right")
        d += elm.Line().at(k4.NO1).right(1.5).label("R86 120R -> JP13 -> NO2  (PCM-side term)", "right")
        d += elm.Line().at(k4.NO2).right(1.5).label("NO2", "right")
        d += elm.Line().at(k4["COIL+"]).left(1.5).label("+5V", "left")
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        u22 = ic(d, (6, -24.5), 6.5, 1.8, "U22 AQY212GS photoMOS (60 V, form A)", left=("LED A", "LED K"), right=("OUT1", "OUT2"), lab_loc="bottom")
        d += elm.Line().at(u22["LED A"]).left(1.5).label("+5V via R97 470R", "left")
        d += elm.Line().at(u22["LED K"]).left(1.5).label("Q4 drain (parallel with coil)", "left")
        d += elm.Line().at(u22.OUT1).right(1.5).label("MCM_CANL", "right")
        d += elm.Line().at(u22.OUT2).right(1.5).label("JP12 -> R96 120R -> MCM_CANH  (MCM-side term)", "right")
        note(d, (0, -29.0),
             "De-energised (board off, reset, crashed) = NC contacts join MCM side to car side: the IMA bus is stock,\n"
             "and both board terminations are disconnected (NO contact open, photoMOS off), so the stock bus sees no extra load.\n"
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
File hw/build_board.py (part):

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c("C2", "10u 50V", "VBAT_P", "GND", (73.0, 40.0), 90, fp=C1206)
c("C3", "10u 50V", "VBAT_P", "GND", (76.0, 40.0), 90, fp=C1206)
c("C4", "10u 50V", "VBAT_P", "GND", (75.0, 44.0), 90, fp=C1206)
c("C47", "10u 50V", "VBAT_P", "GND", (64.0, 58.5), 180, fp=C1206)  # buck input cap at U2's VIN/GND pins
# buck LMR16006 (SOT-23-6: 1 CB, 2 GND, 3 FB, 4 EN, 5 VIN, 6 SW)
part("U2", ("Package_TO_SOT_SMD", "SOT-23-6"), "LMR16006Y-Q1", "LMR16006YQDDCRQ1",
     {"1": "BUCK_CB", "2": "GND", "3": "BUCK_FB", "4": "VBAT_P", "5": "VBAT_P", "6": "BUCK_SW"}, (58.0, 58.0), 0)
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    PARTS[ref].update(val="330 1W", mpn="25121WJ0331T4E 330R 1W 2512", nets=nets)
for ref in ("RF3", "RF4"):
    PARTS[ref].update(val="10k 1W", mpn="25121WF1002T4E 10k 1W 2512 1%")
# DAC_D (U14 pin 9, top right) to its summing resistor above U14 rather than across the DAC_A-C fan-out
PARTS["R40"]["pos"], PARTS["R40"]["rot"] = (60.0, 11.45), 0
# fewer feeders: C41 onto the 1 nF 0603 already used, every 100 nF on the one 0603 50 V X7R
PARTS["C41"].update(fp=("Capacitor_SMD", "C_0603_1608Metric"), mpn="1n 0603 X7R")
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

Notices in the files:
README.md:
Licence:
- **Hardware** (everything in `hw/`, including the scripts that generate the board, and the images):
[CERN-OHL-P-2.0](LICENSES/CERN-OHL-P-2.0.txt).
- **Software** (tests and image scripts): [MIT](LICENSES/MIT.txt).
No warranty. This connects to a high-voltage traction pack; building and using it is at your own risk.
